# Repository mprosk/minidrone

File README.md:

# Minidrone

Minidrone is a drone module with a built in Attack/Release amp envelope. It contains five sawtooth oscillators each with individual pitch control and an enable switch. A master pitch control can adjust the tuning of all voices at once. 

Loosely inspired on the Elta Music Solar50

## Case

- 1/2" x 3.5" sheet
  - 2 @ 6.25"
  - 2 @ 13.8"
- 1/4" x 2.5" sheet
  - 2 @ 13.8"
- 1/2" ply
  - 1 @ 13.8" x 5.25"

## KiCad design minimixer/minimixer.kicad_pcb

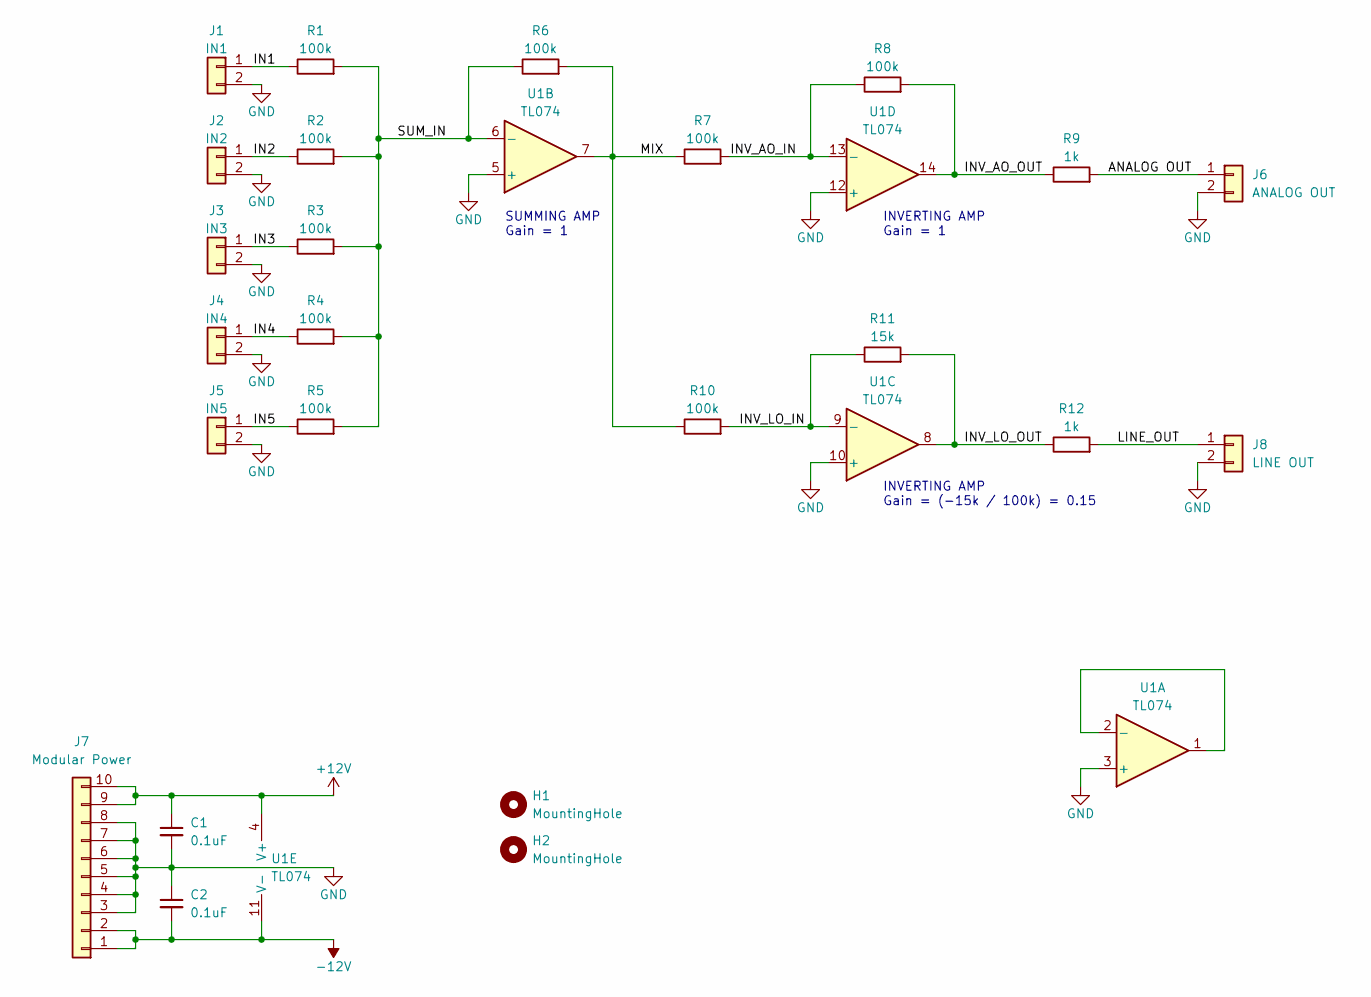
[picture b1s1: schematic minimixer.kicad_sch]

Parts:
C1, C2: 0.1uF; C_Disc_D3.0mm_W1.6mm_P2.50mm
H1, H2: MountingHole; MountingHole_3.2mm_M3
J1: IN1; Molex_KK-254_AE-6410-02A_1x02_P2.54mm_Vertical
J2: IN2; Molex_KK-254_AE-6410-02A_1x02_P2.54mm_Vertical
J3: IN3; Molex_KK-254_AE-6410-02A_1x02_P2.54mm_Vertical
J4: IN4; Molex_KK-254_AE-6410-02A_1x02_P2.54mm_Vertical
J5: IN5; Molex_KK-254_AE-6410-02A_1x02_P2.54mm_Vertical
J6: ANALOG OUT; Molex_KK-254_AE-6410-02A_1x02_P2.54mm_Vertical
J7: Modular Power; IDC-Header_2x05_P2.54mm_Vertical
J8: LINE OUT; Molex_KK-254_AE-6410-02A_1x02_P2.54mm_Vertical
R1, R2, R3, R4, R5, R6, R7, R10: 100k; R_Axial_DIN0207_L6.3mm_D2.5mm_P10.16mm_Horizontal
R8: 100k; R_Axial_DIN0207_L6.3mm_D2.5mm_P2.54mm_Vertical
R9, R12: 1k; R_Axial_DIN0207_L6.3mm_D2.5mm_P2.54mm_Vertical
R11: 15k; R_Axial_DIN0207_L6.3mm_D2.5mm_P2.54mm_Vertical
U1: TL074; DIP-14_W10.16mm

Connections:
+12V: C1.1, J7.9, J7.10, U1.4 (V+)
-12V: C2.2, J7.1, J7.2, U1.11 (V-)
/ANALOG OUT: J6.1, R9.2
/IN1: J1.1, R1.1
/IN2: J2.1, R2.1
/IN3: J3.1, R3.1
/IN4: J4.1, R4.1
/IN5: J5.1, R5.1
/INV_AO_IN: R7.2, R8.1, U1.13 (-)
/INV_AO_OUT: R8.2, R9.1, U1.14
/INV_LO_IN: R10.2, R11.1, U1.9 (-)
/INV_LO_OUT: R11.2, R12.1, U1.8
/LINE_OUT: J8.1, R12.2
/MIX: R6.2, R7.1, R10.1, U1.7
/SUM_IN: R1.2, R2.2, R3.2, R4.2, R5.2, R6.1, U1.6 (-)
GND: C1.2, C2.1, J1.2, J2.2, J3.2, J4.2, J5.2, J6.2, J7.3, J7.4, J7.5, J7.6, J7.7, J7.8, J8.2, U1.3 (+), U1.5 (+), U1.10 (+), U1.12 (+)
unnamed: U1.1, U1.2 (-)

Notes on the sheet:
INVERTING AMP Gain = (-15k / 100k) = 0.15
SUMMING AMP Gain = 1
INVERTING AMP Gain = 1

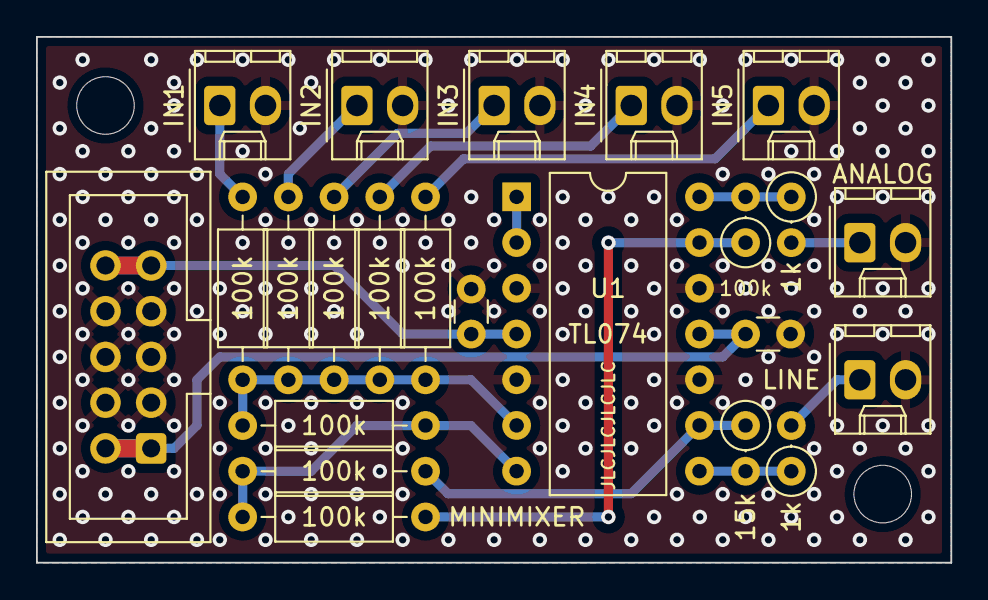
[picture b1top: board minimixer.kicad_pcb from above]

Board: 2 copper layers, 50.8 x 29.2 mm, 25 parts (0 on the bottom side), 17 nets.

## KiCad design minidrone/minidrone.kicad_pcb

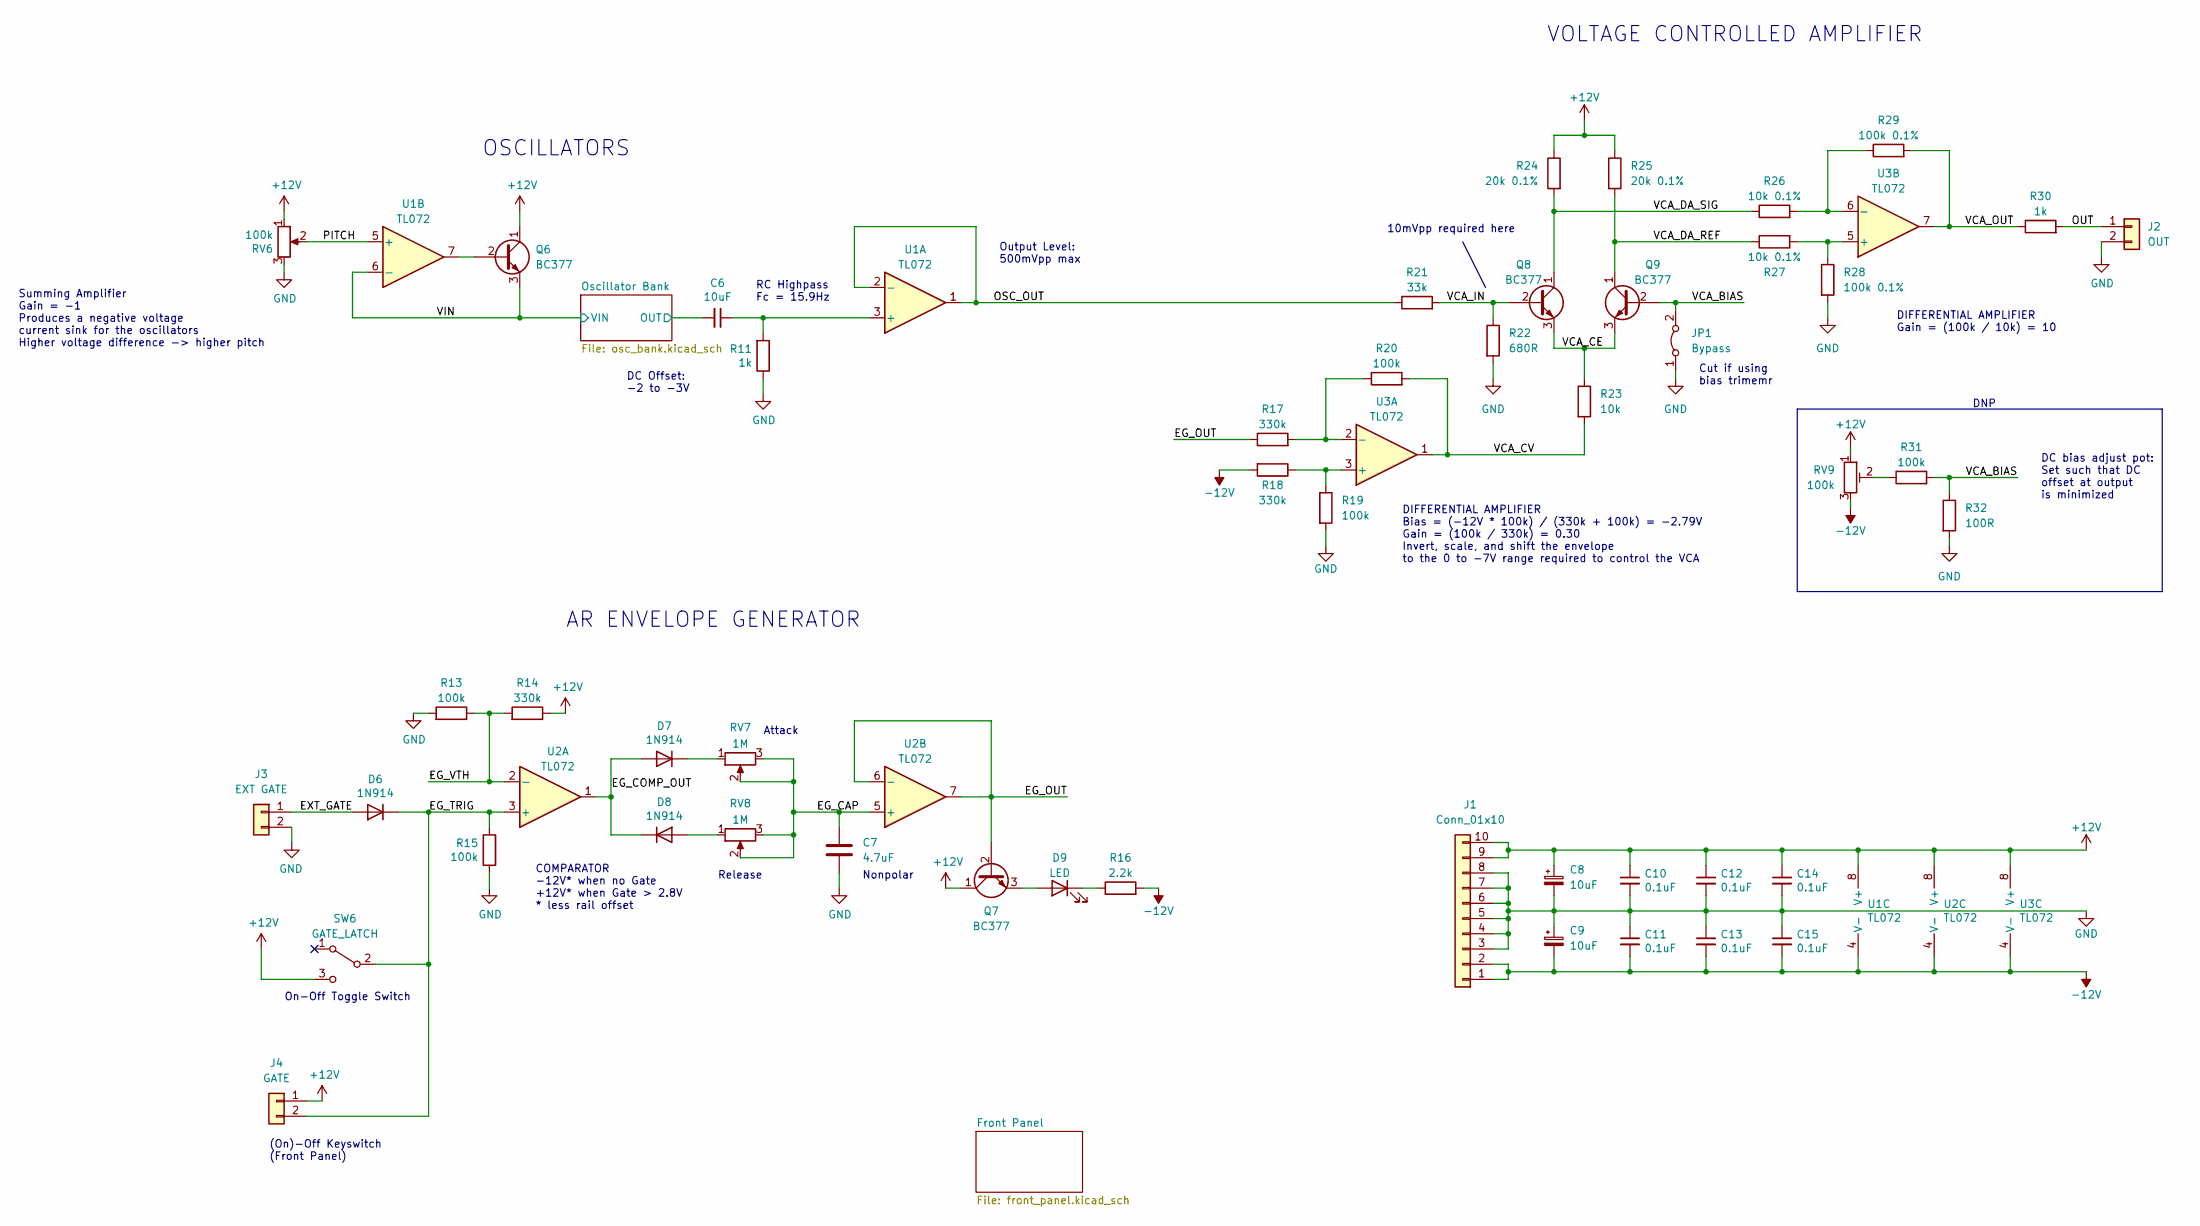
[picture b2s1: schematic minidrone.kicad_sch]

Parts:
C6: 10uF; C_Disc_D3.0mm_W1.6mm_P2.50mm
C7: 4.7uF; C_Disc_D3.0mm_W1.6mm_P2.50mm
C8, C9: 10uF; CP_Radial_D5.0mm_P2.50mm
C10, C11, C12, C13, C14, C15: 0.1uF; C_Disc_D3.0mm_W1.6mm_P2.50mm
D6, D7, D8: 1N914; D_DO-35_SOD27_P7.62mm_Horizontal
D9: LED; LED_D5.0mm
J1: Conn_01x10; IDC-Header_2x05_P2.54mm_Vertical
J2: OUT; Molex_KK-254_AE-6410-02A_1x02_P2.54mm_Vertical
J3: EXT GATE; Molex_KK-254_AE-6410-02A_1x02_P2.54mm_Vertical
J4: GATE; Molex_KK-254_AE-6410-02A_1x02_P2.54mm_Vertical
JP1: Bypass; SolderJumper-2_P1.3mm_Bridged_RoundedPad1.0x1.5mm
Q6, Q7, Q8, Q9: BC377; TO-92L_Inline_Wide
R11, R30: 1k; R_Axial_DIN0207_L6.3mm_D2.5mm_P10.16mm_Horizontal
R13, R15, R19, R20: 100k; R_Axial_DIN0207_L6.3mm_D2.5mm_P10.16mm_Horizontal
R14, R17, R18: 330k; R_Axial_DIN0207_L6.3mm_D2.5mm_P10.16mm_Horizontal
R16: 2.2k; R_Axial_DIN0207_L6.3mm_D2.5mm_P10.16mm_Horizontal
R21: 33k; R_Axial_DIN0207_L6.3mm_D2.5mm_P10.16mm_Horizontal
R22: 680R; R_Axial_DIN0207_L6.3mm_D2.5mm_P10.16mm_Horizontal
R23: 10k; R_Axial_DIN0207_L6.3mm_D2.5mm_P10.16mm_Horizontal
R24, R25: 20k 0.1%; R_Axial_DIN0207_L6.3mm_D2.5mm_P10.16mm_Horizontal
R26, R27: 10k 0.1%; R_Axial_DIN0207_L6.3mm_D2.5mm_P10.16mm_Horizontal
R28, R29: 100k 0.1%; R_Axial_DIN0207_L6.3mm_D2.5mm_P10.16mm_Horizontal
R31: 100k; R_Axial_DIN0207_L6.3mm_D2.5mm_P2.54mm_Vertical
R32: 100R; R_Axial_DIN0207_L6.3mm_D2.5mm_P2.54mm_Vertical
RV6: 100k; Bourns_PVT09A
RV7, RV8: 1M; Bourns_PDB12-H
RV9: 100k; Potentiometer_Bourns_3296Y_Vertical
SW6: GATE_LATCH; Switch_SPDT
U1, U2, U3: TL072; DIP-8_W7.62mm

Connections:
+12V: C8.1, C10.1, C12.1, C14.1, J1.9, J1.10, J4.1, Q6.1 (C), Q7.1 (C), R14.1, R24.1, R25.1, RV6.1, RV9.1, SW6.3 (C), U1.8 (V+), U2.8 (V+), U3.8 (V+)
-12V: C9.2, C11.2, C13.2, C15.2, J1.1, J1.2, R16.2, R18.2, RV9.3, U1.4 (V-), U2.4 (V-), U3.4 (V-); also elsewhere on the board
/EG_CAP: C7.1, RV7.2, RV7.3, RV8.2, RV8.3, U2.5 (+)
/EG_COMP_OUT: D7.2 (A), D8.1 (K), U2.1
/EG_OUT: Q7.2 (B), R17.1, U2.6 (-), U2.7
/EG_TRIG: D6.1 (K), J4.2, R15.1, SW6.2 (B), U2.3 (+)
/EG_VTH: R13.1, R14.2, U2.2 (-)
/EXT_GATE: D6.2 (A), J3.1
/OSC_OUT: R21.1, U1.1, U1.2 (-)
/OUT: J2.1, R30.2
/Oscillator Bank/OUT: C6.2; also elsewhere on the board
/PITCH: RV6.2, U1.5 (+)
/VCA_BIAS: JP1.2 (B), Q9.2 (B), R31.2, R32.1
/VCA_CE: Q8.3 (E), Q9.3 (E), R23.1
/VCA_CV: R20.2, R23.2, U3.1
/VCA_DA_REF: Q9.1 (C), R25.2, R27.1
/VCA_DA_SIG: Q8.1 (C), R24.2, R26.1
/VCA_IN: Q8.2 (B), R21.2, R22.1
/VCA_OUT: R29.2, R30.1, U3.7
/VIN: Q6.3 (E), U1.6 (-); also elsewhere on the board
GND: C7.2, C8.2, C9.1, C10.2, C11.1, C12.2, C13.1, C14.2, C15.1, J1.3, J1.4, J1.5, J1.6, J1.7, J1.8, J2.2, J3.2, JP1.1 (A), R11.1, R13.2, R15.2, R19.2, R22.2, R28.2, R32.2, RV6.3
unnamed: C6.1, R11.2, U1.3 (+)
unnamed: D7.1 (K), RV7.1
unnamed: D8.2 (A), RV8.1
unnamed: D9.1 (K), R16.1
unnamed: D9.2 (A), Q7.3 (E)
unnamed: Q6.2 (B), U1.7
unnamed: R17.2, R20.1, U3.2 (-)
unnamed: R18.1, R19.1, U3.3 (+)
unnamed: R26.2, R29.1, U3.6 (-)
unnamed: R27.2, R28.1, U3.5 (+)
unnamed: R31.1, RV9.2

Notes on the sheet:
On-Off Toggle Switch
DC bias adjust pot: Set such that DC offset at output is minimized
COMPARATOR -12V* when no Gate +12V* when Gate > 2.8V * less rail offset
Release
AR ENVELOPE GENERATOR
OSCILLATORS
VOLTAGE CONTROLLED AMPLIFIER
DIFFERENTIAL AMPLIFIER Bias = (-12V * 100k) / (330k + 100k) = -2.79V Gain = (100k / 330k) = 0.30 Invert, scale, and shift the envelope to the 0 to -7V range required to control the VCA
DIFFERENTIAL AMPLIFIER Gain = (100k / 10k) = 10
DNP
Summing Amplifier Gain = -1 Produces a negative voltage current sink for the oscillators Higher voltage difference -> higher pitch
RC Highpass Fc = 15.9Hz
DC Offset: -2 to -3V
Attack
Output Level: 500mVpp max
10mVpp required here
Nonpolar
Cut if using bias trimemr
(On)-Off Keyswitch (Front Panel)

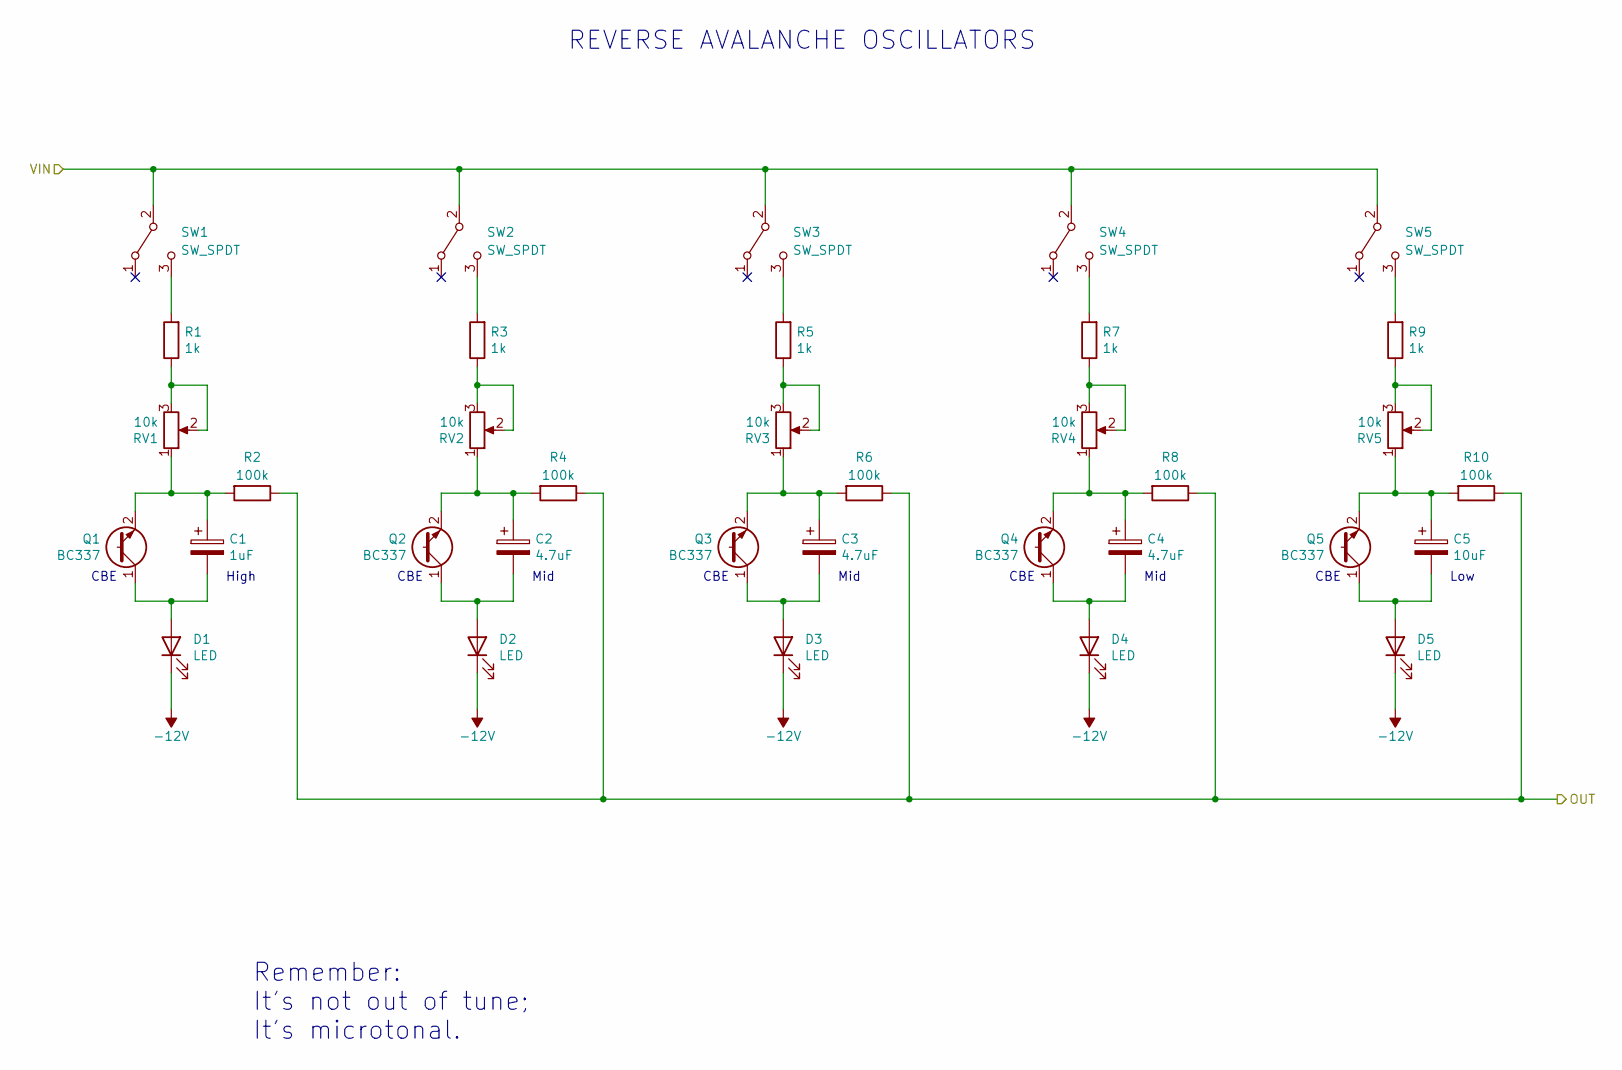
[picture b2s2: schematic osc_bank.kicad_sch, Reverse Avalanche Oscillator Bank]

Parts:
C1: 1uF; CP_Radial_D5.0mm_P2.50mm
C2, C3, C4: 4.7uF; CP_Radial_D5.0mm_P2.50mm
C5: 10uF; CP_Radial_D5.0mm_P2.50mm
D1, D2, D3, D4, D5: LED; LED_D5.0mm
Q1, Q2, Q3, Q4, Q5: BC337; TO-92-2
R1, R3, R5, R7, R9: 1k; R_Axial_DIN0207_L6.3mm_D2.5mm_P10.16mm_Horizontal
R2, R4, R6, R8, R10: 100k; R_Axial_DIN0207_L6.3mm_D2.5mm_P10.16mm_Horizontal
RV1, RV2, RV3, RV4, RV5: 10k; Bourns_PVT09A
SW1, SW2, SW3, SW4, SW5: SW_SPDT; Switch_SPDT

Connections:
-12V: D1.1 (K), D2.1 (K), D3.1 (K), D4.1 (K), D5.1 (K); also elsewhere on the board
/Oscillator Bank/OUT: R2.1, R4.1, R6.1, R8.1, R10.1; also elsewhere on the board
/VIN: SW1.2 (B), SW2.2 (B), SW3.2 (B), SW4.2 (B), SW5.2 (B); also elsewhere on the board
unnamed: C1.1, Q1.2 (E), R2.2, RV1.1
unnamed: C1.2, D1.2 (A), Q1.1 (C)
unnamed: C2.1, Q2.2 (E), R4.2, RV2.1
unnamed: C2.2, D2.2 (A), Q2.1 (C)
unnamed: C3.1, Q3.2 (E), R6.2, RV3.1
unnamed: C3.2, D3.2 (A), Q3.1 (C)
unnamed: C4.1, Q4.2 (E), R8.2, RV4.1
unnamed: C4.2, D4.2 (A), Q4.1 (C)
unnamed: C5.1, Q5.2 (E), R10.2, RV5.1
unnamed: C5.2, D5.2 (A), Q5.1 (C)
unnamed: R1.1, RV1.2, RV1.3
unnamed: R1.2, SW1.3 (C)
unnamed: R3.1, RV2.2, RV2.3
unnamed: R3.2, SW2.3 (C)
unnamed: R5.1, RV3.2, RV3.3
unnamed: R5.2, SW3.3 (C)
unnamed: R7.1, RV4.2, RV4.3
unnamed: R7.2, SW4.3 (C)
unnamed: R9.1, RV5.2, RV5.3
unnamed: R9.2, SW5.3 (C)

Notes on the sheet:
Mid
CBE
High
Remember: It's not out of tune; It's microtonal.
Low
REVERSE AVALANCHE OSCILLATORS

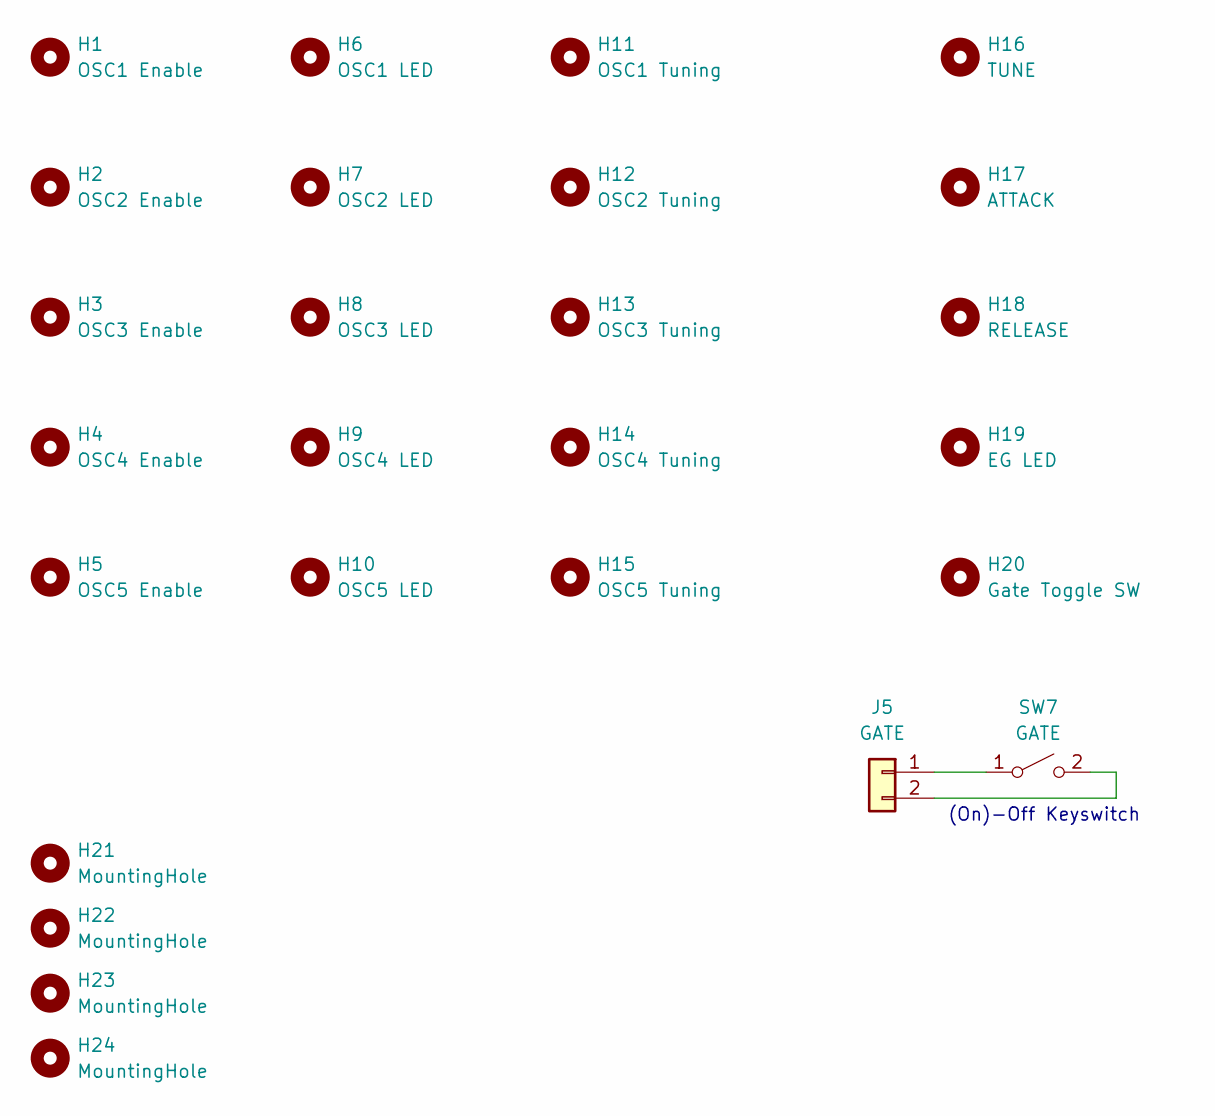
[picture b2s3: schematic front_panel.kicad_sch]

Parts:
H1: OSC1 Enable; Hole_Toggle_Switch
H2: OSC2 Enable; Hole_Toggle_Switch
H3: OSC3 Enable; Hole_Toggle_Switch
H4: OSC4 Enable; Hole_Toggle_Switch
H5: OSC5 Enable; Hole_Toggle_Switch
H6: OSC1 LED; Hole_LED_5mm
H7: OSC2 LED; Hole_LED_5mm
H8: OSC3 LED; Hole_LED_5mm
H9: OSC4 LED; Hole_LED_5mm
H10: OSC5 LED; Hole_LED_5mm
H11: OSC1 Tuning; Hole_Pot
H12: OSC2 Tuning; Hole_Pot
H13: OSC3 Tuning; Hole_Pot
H14: OSC4 Tuning; Hole_Pot
H15: OSC5 Tuning; Hole_Pot
H16: TUNE; Hole_Pot
H17: ATTACK; Hole_Pot
H18: RELEASE; Hole_Pot
H19: EG LED; Hole_LED_5mm
H20: Gate Toggle SW; Hole_Toggle_Switch
H21, H22, H23, H24: MountingHole; MountingHole_3.2mm_M3
J5: GATE; SMD_Connector
SW7: GATE; SW_Kailh_Choc_1.00u_PCB

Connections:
unnamed: J5.1, SW7.1 (A)
unnamed: J5.2, SW7.2 (B)

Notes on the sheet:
(On)-Off Keyswitch

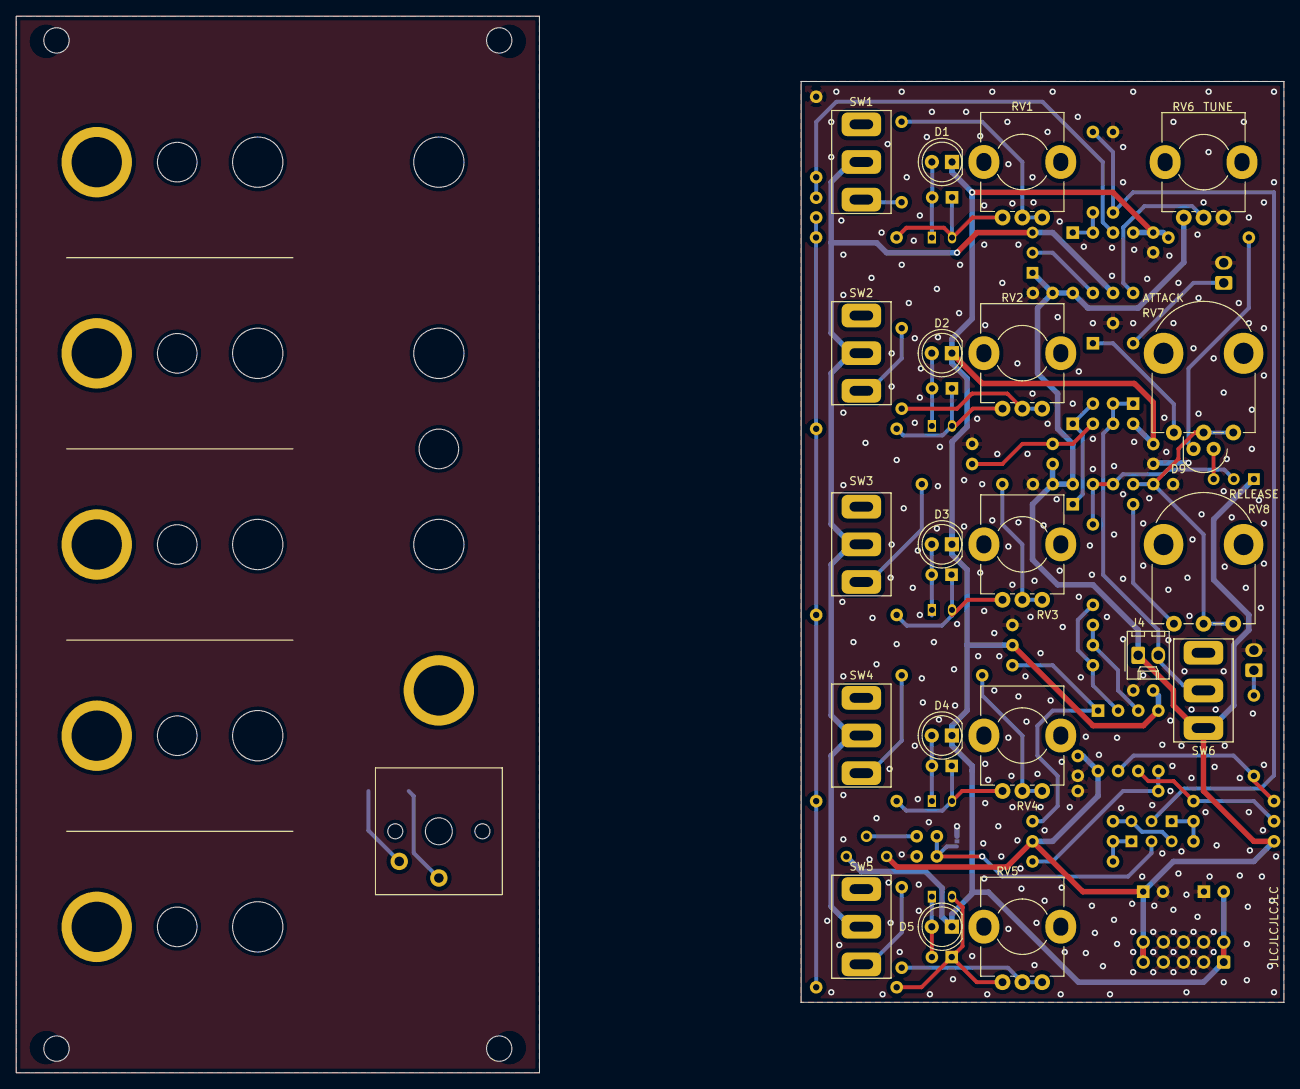
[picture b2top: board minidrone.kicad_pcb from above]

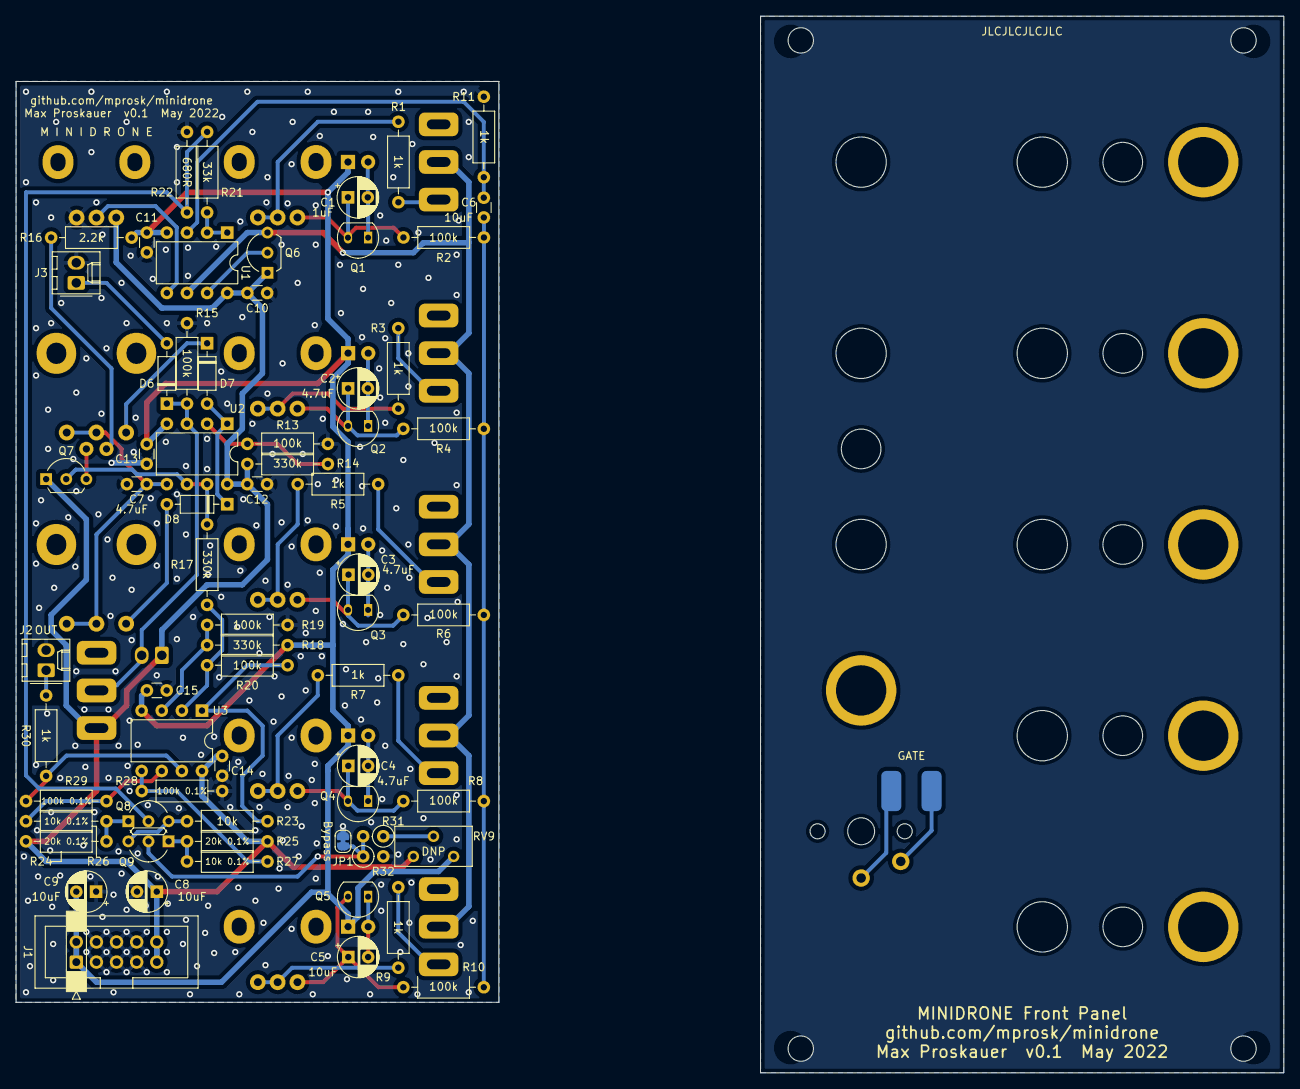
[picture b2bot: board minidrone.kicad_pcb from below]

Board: 2 copper layers, 160.0 x 133.3 mm, 113 parts (67 on the bottom side), 54 nets.

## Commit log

2022-05-02 Copy contents from other repo
2022-05-12 Correct pot footprints. continue layout
2022-05-13 Continue layout
2022-05-13 Add 3d model of case
2022-05-13 Complete layout
2022-05-13 Start front panel
2022-05-17 Include proper library references
2022-05-17 Lay out front panel. WIP updating mainboard layout
2022-05-23 Complete initial layout
2022-05-27 Complete cosmetics layout
2022-05-27 Generated rounded version. Export gerbers
2022-05-27 Export gerbers
2022-05-27 Export schematic to PDF
2022-06-01 Begin layout of minidrone aux panel
2022-06-03 Add minimixer board
2022-06-05 Complete aux panel PCB
2022-06-06 Finalize case design
2022-06-17 Fix schematic issues identified in first production run. PCB fixes TODO!
2022-06-22 Add image to readme
2023-06-23 Add gerber files for aluminum aux panel
